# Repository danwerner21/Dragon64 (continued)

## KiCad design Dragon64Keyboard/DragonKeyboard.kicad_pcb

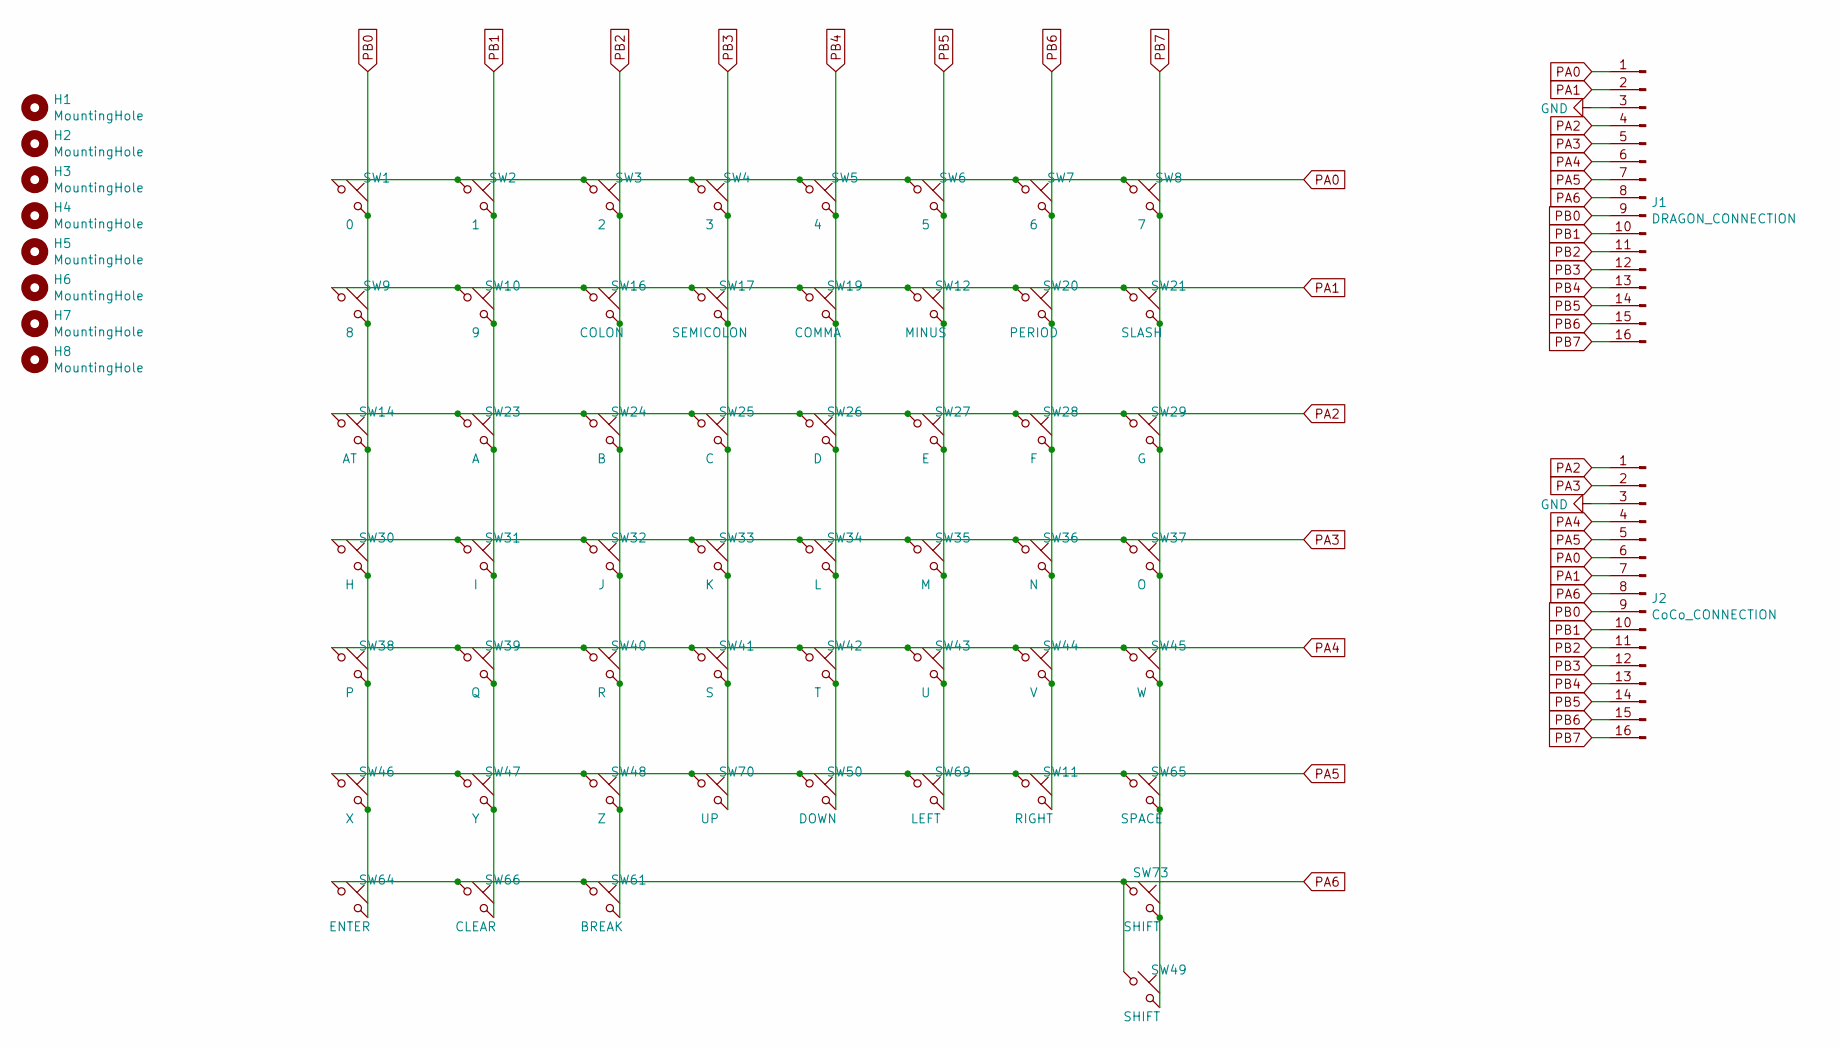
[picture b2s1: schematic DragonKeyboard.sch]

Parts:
H1, H2, H3, H4, H5, H6, H7, H8: MountingHole; MountingHole_3.2mm_M3_Pad
J1: DRAGON_CONNECTION; PinHeader_1x16_P2.54mm_Vertical
J2: CoCo_CONNECTION; PinHeader_1x16_P2.54mm_Vertical
SW1: 0; CHERRY_PCB_100H
SW2: 1; CHERRY_PCB_100H
SW3: 2; CHERRY_PCB_100H
SW4: 3; CHERRY_PCB_100H
SW5: 4; CHERRY_PCB_100H
SW6: 5; CHERRY_PCB_100H
SW7: 6; CHERRY_PCB_100H
SW8: 7; CHERRY_PCB_100H
SW9: 8; CHERRY_PCB_100H
SW10: 9; CHERRY_PCB_100H
SW11: RIGHT; CHERRY_PCB_100H
SW12: MINUS; CHERRY_PCB_100H
SW14: AT; CHERRY_PCB_100H
SW16: COLON; CHERRY_PCB_100H
SW17: SEMICOLON; CHERRY_PCB_100H
SW19: COMMA; CHERRY_PCB_100H
SW20: PERIOD; CHERRY_PCB_100H
SW21: SLASH; CHERRY_PCB_100H
SW23: A; CHERRY_PCB_100H
SW24: B; CHERRY_PCB_100H
SW25: C; CHERRY_PCB_100H
SW26: D; CHERRY_PCB_100H
SW27: E; CHERRY_PCB_100H
SW28: F; CHERRY_PCB_100H
SW29: G; CHERRY_PCB_100H
SW30: H; CHERRY_PCB_100H
SW31: I; CHERRY_PCB_100H
SW32: J; CHERRY_PCB_100H
SW33: K; CHERRY_PCB_100H
SW34: L; CHERRY_PCB_100H
SW35: M; CHERRY_PCB_100H
SW36: N; CHERRY_PCB_100H
SW37: O; CHERRY_PCB_100H
SW38: P; CHERRY_PCB_100H
SW39: Q; CHERRY_PCB_100H
SW40: R; CHERRY_PCB_100H
SW41: S; CHERRY_PCB_100H
SW42: T; CHERRY_PCB_100H
SW43: U; CHERRY_PCB_100H
SW44: V; CHERRY_PCB_100H
SW45: W; CHERRY_PCB_100H
SW46: X; CHERRY_PCB_100H
SW47: Y; CHERRY_PCB_100H
SW48: Z; CHERRY_PCB_100H
SW49: SHIFT; CHERRY_PCB_225H
SW50: DOWN; SW_Cherry_MX_1.00u_PCB
SW61: BREAK; SW_Cherry_MX_1.75u_PCB
SW64: ENTER; CHERRY_PCB_225H
SW65: SPACE; CHERRY_PCB_625H
SW66: CLEAR; CHERRY_PCB_100H
SW69: LEFT; CHERRY_PCB_100H
SW70: UP; CHERRY_PCB_100H
SW73: SHIFT; CHERRY_PCB_275H

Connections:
GND: J1.3, J2.3
PA0: J1.1, J2.6, SW1.1, SW2.1, SW3.1, SW4.1, SW5.1, SW6.1, SW7.1, SW8.1
PA1: J1.2, J2.7, SW9.1, SW10.1, SW12.1, SW16.1, SW17.1, SW19.1, SW20.1, SW21.1
PA2: J1.4, J2.1, SW14.1, SW23.1, SW24.1, SW25.1, SW26.1, SW27.1, SW28.1, SW29.1
PA3: J1.5, J2.2, SW30.1, SW31.1, SW32.1, SW33.1, SW34.1, SW35.1, SW36.1, SW37.1
PA4: J1.6, J2.4, SW38.1, SW39.1, SW40.1, SW41.1, SW42.1, SW43.1, SW44.1, SW45.1
PA5: J1.7, J2.5, SW11.1, SW46.1, SW47.1, SW48.1, SW50.1, SW65.1, SW69.1, SW70.1
PA6: J1.8, J2.8, SW49.1, SW61.1, SW64.1, SW66.1, SW73.1
PB0: J1.9, J2.9, SW1.2, SW9.2, SW14.2, SW30.2, SW38.2, SW46.2, SW64.2
PB1: J1.10, J2.10, SW2.2, SW10.2, SW23.2, SW31.2, SW39.2, SW47.2, SW66.2
PB2: J1.11, J2.11, SW3.2, SW16.2, SW24.2, SW32.2, SW40.2, SW48.2, SW61.2
PB3: J1.12, J2.12, SW4.2, SW17.2, SW25.2, SW33.2, SW41.2, SW70.2
PB4: J1.13, J2.13, SW5.2, SW19.2, SW26.2, SW34.2, SW42.2, SW50.2
PB5: J1.14, J2.14, SW6.2, SW12.2, SW27.2, SW35.2, SW43.2, SW69.2
PB6: J1.15, J2.15, SW7.2, SW11.2, SW20.2, SW28.2, SW36.2, SW44.2
PB7: J1.16, J2.16, SW8.2, SW21.2, SW29.2, SW37.2, SW45.2, SW49.2, SW65.2, SW73.2

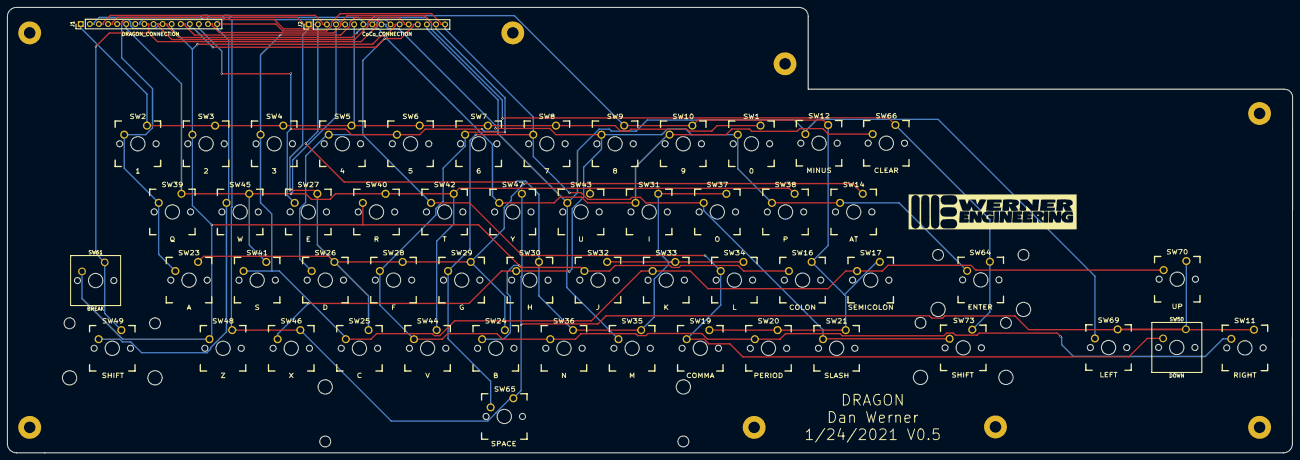
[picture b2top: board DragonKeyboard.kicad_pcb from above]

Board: 2 copper layers, 359.1 x 124.5 mm, 63 parts (0 on the bottom side), 16 nets.

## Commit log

2022-03-11 PAL to NTSC
2022-04-10 Bug fixes and add Floppy Controller
2022-04-11 add case
2022-04-11 enclosure design work
2022-04-13 PCB layout work
2022-04-22 pcb cleanup and readme
2022-04-27 pcb routing
2022-04-29 enclosure changes
2022-05-03 enclosure
2022-05-30 add rom images
2022-05-30 update schematic and enclosure
2022-05-30 add keycap template
2022-06-09 documentation update
2022-06-23 PCB updates
2022-07-02 version 1.0 cleanup
2022-07-05 update docs
2022-07-14 updated images
2023-10-14 update BOM
